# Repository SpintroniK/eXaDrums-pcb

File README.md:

# eXaDrums-pcb

Components list: 

 * MCP3008 x1 (U1) - https://fr.farnell.com/microchip/mcp3008-i-sl/10bit-adc-8-ch-spi-smd-soic16/dp/1292241
 * LMC7660 x1 (U2) - https://fr.farnell.com/texas-instruments/lmc7660im-nopb/convertisseur-dc-dc-charge-pump/dp/1469158
 * TLC2264 x2 (U3, U4) - https://fr.farnell.com/texas-instruments/tlc2264cdr/ampli-op-710khz-0-55v-us-soic/dp/2782837
 * 100k resistors x24 (R1 to 224) - https://fr.farnell.com/multicomp/mcsr08x1003ftl/res-ceramique-100k-1-0-125w-0805/dp/2074335
 * 1M potentiometers x8 (RV1 to RV8) - https://fr.farnell.com/bourns/3314g-2-105e/potentiometre-trimmer-1m-20-1/dp/2328478
 * 10µF capacitors x2 (C1, C2) - https://fr.farnell.com/vishay/tmcp1a106ktrf/condensateur-tantale-10uf-10v/dp/2491435
 * 10µF capacitor x1 (C3) - https://fr.farnell.com/kemet/c0805c106m9racauto/condensateur-10-f-6-3v-20-x7r/dp/2776884
 * 220nF capacitor x1 (C4) - https://fr.farnell.com/yageo/cc0805krx7r7bb224/condensateur-mlcc-x7r-220nf-16v/dp/644183
 * Board-To-Board Connector - https://fr.farnell.com/wurth-elektronik/61304021821/connect-femelle-40-voies-2-rangs/dp/2827916
 * D Sub Connector - https://fr.farnell.com/norcomp/171-025-213r001/sub-d-embase-a-souder-droit-25voies/dp/2294252

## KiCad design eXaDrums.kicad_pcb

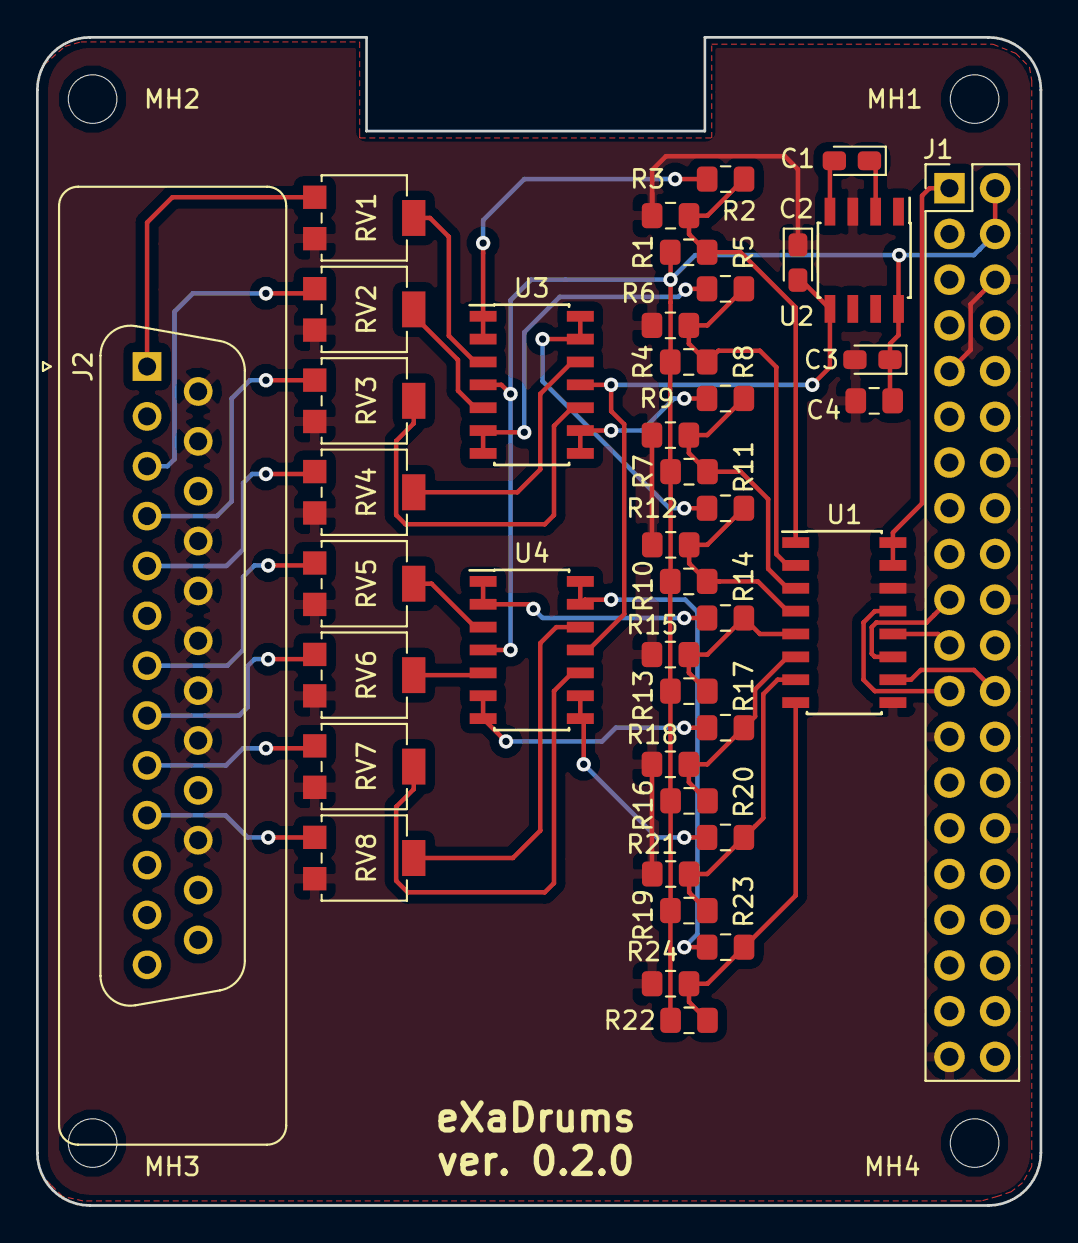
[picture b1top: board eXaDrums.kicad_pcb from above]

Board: 2 copper layers, 55.8 x 64.9 mm, 46 parts (0 on the bottom side), 42 nets.

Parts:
C1, C2, C3: 10uF; CP_EIA-2012-12_Kemet-R_Pad1.30x1.05mm_HandSolder
C4: 220nF; C_0805_2012Metric_Pad1.15x1.40mm_HandSolder
J1: Conn_02x20_Odd_Even; PinHeader_2x20_P2.54mm_Vertical
J2: DB25_Female; DSUB-25_Female_Vertical_P2.77x2.84mm
MH1, MH2, MH3, MH4: MountingHole; MountingHole_2.7mm_M2.5
R1, R2, R3, R4, R5, R6, R7, R8, R9, R10, R11, R12, R13, R14, R15, R16, R17, R18, R19, R20, R21, R22, R23, R24: R; R_0805_2012Metric_Pad1.15x1.40mm_HandSolder
RV1, RV2, RV3, RV4, RV5, RV6, RV7, RV8: R_POT; Potentiometer_Bourns_3314G_Vertical
U1: MCP3008; SOIC-16_3.9x9.9mm_P1.27mm
U2: ICL7660; SOIC-8_3.9x4.9mm_P1.27mm
U3, U4: TLC274; SOIC-14_3.9x8.7mm_P1.27mm

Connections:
+3V3: J1.1, U1.15, U1.16
+5V: C3.1, C4.1, J1.2, J1.4, R1.2, R4.2, R7.2, R10.2, R13.2, R16.2, R19.2, R22.2, U2.8, U3.4, U4.4
CLK: J1.23, U1.13
CS0: J1.24, U1.10
GND: C2.1, C3.2, C4.2, J1.6, J1.9, J1.14, J1.20, J1.25, J1.30, J1.34, J1.39, J2.14, J2.15, J2.17, J2.18, J2.19, J2.20, J2.21, J2.23, R3.1, R6.1, R9.1, R12.1, R15.1, R18.1, R21.1, R24.1, RV1.3, RV2.3, RV3.3, RV4.3, RV5.3, RV6.3, RV7.3, RV8.3, U1.9, U1.14, U2.3
MISO: J1.21, U1.12
MOSI: J1.19, U1.11
unnamed: C1.1, U2.2
unnamed: C1.2, U2.4
unnamed: J2.1, RV1.1
unnamed: J2.3, RV2.1
unnamed: J2.4, RV3.1
unnamed: J2.5, RV4.1
unnamed: J2.7, RV5.1
unnamed: J2.8, RV6.1
unnamed: J2.9, RV7.1
unnamed: J2.10, RV8.1
unnamed: R1.1, R2.1, R3.2, U1.1
unnamed: R2.2, U3.1, U3.2
unnamed: R4.1, R5.1, R6.2, U1.2
unnamed: R5.2, U3.6, U3.7
unnamed: R7.1, R8.1, R9.2, U1.3
unnamed: R8.2, U3.8, U3.9
unnamed: R10.1, R11.1, R12.2, U1.4
unnamed: R11.2, U3.13, U3.14
unnamed: R13.1, R14.1, R15.2, U1.5
unnamed: R14.2, U4.1, U4.2
unnamed: R16.1, R17.1, R18.2, U1.6
unnamed: R17.2, U4.6, U4.7
unnamed: R19.1, R20.1, R21.2, U1.7
unnamed: R20.2, U4.8, U4.9
unnamed: R22.1, R23.1, R24.2, U1.8
unnamed: R23.2, U4.13, U4.14
unnamed: RV1.2, U3.3
unnamed: RV2.2, U3.5
unnamed: RV3.2, U3.10
unnamed: RV4.2, U3.12
unnamed: RV5.2, U4.3
unnamed: RV6.2, U4.5
unnamed: RV7.2, U4.10
unnamed: RV8.2, U4.12
Vee: C2.2, U2.5, U3.11, U4.11

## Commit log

2018-09-05 First working prototype. Boards ordered from OSH Park.
2018-09-08 Version 0.2.0: New board layout, and DB25 connector.
2018-09-30 Create LICENSE
